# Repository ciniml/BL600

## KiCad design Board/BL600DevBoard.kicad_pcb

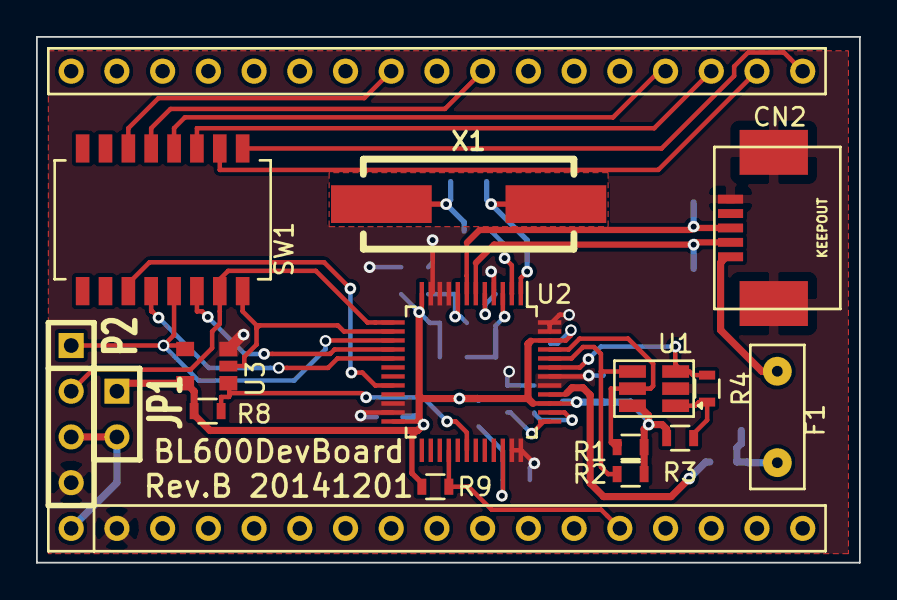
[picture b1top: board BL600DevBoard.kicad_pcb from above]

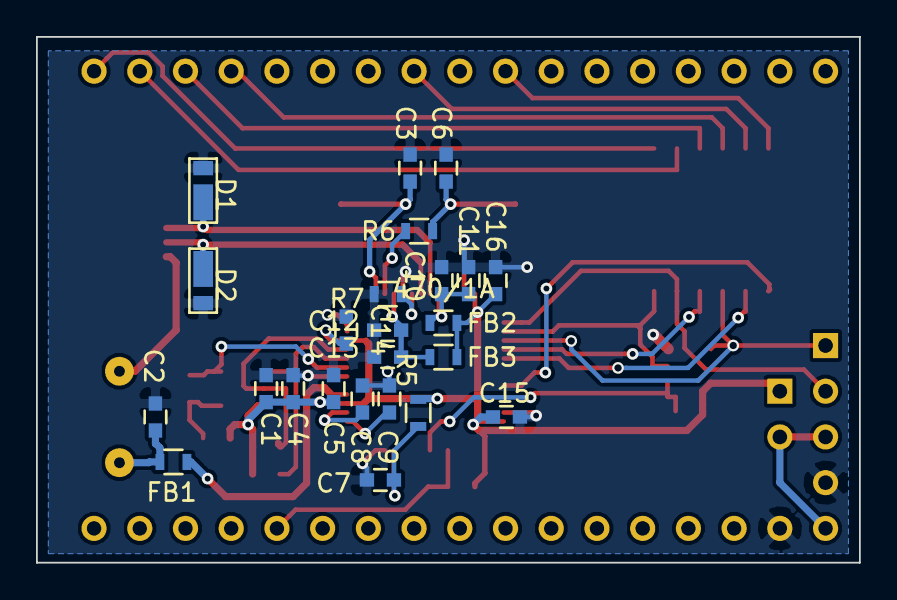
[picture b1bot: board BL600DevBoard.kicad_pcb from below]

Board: 2 copper layers, 45.7 x 29.2 mm, 40 parts (24 on the bottom side), 35 nets.

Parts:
C1, C2, C7, C9: 10n; C_0603
C3, C6: 18p; C_0603
C4, C10, C12: 4.7u; C_0603
C5, C8, C11, C13, C14, C15, C16: 100n; C_0603
CN1: Socket_BL600; SOCKET_BL600
CN2: USB-MINI-B; HIROSE_UX60SC-MB-5ST
D1, D2: UDZV15B; Diode-TUMD2
F1: RXEF050
FB1, FB2, FB3: 470/1A; R_0603
JP1: JUMPER; SIL-2
P2: CONN_BL600_SWDIF; SIL-4
R1, R2, R3, R5, R8, R9: 10k; R_0603
R4: 2k; R_0603
R6: 51; R_0603
R7: 12k; R_0603
SW1: DIPSW_8; 57D-0803
U1: 93C56; SOT-23-6
U2: FT232H; LQFP-48_7x7mm_Pitch0.5mm
U3: TC7SZ125; SC-74A
X1: 12M; Crystal_HC49-SD_SMD

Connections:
/CTS#: SW1.3, U2.16
/DTR#: SW1.5, U2.17
/RI#: SW1.6, U2.20
/SWDCLK_TxD: P2.2, SW1.2, U2.13
/SWDIO_OE: R8.2, U2.30, U3.1
/TDI_RxD: SW1.1, U2.14, U3.2
/TDO_RTS#: P2.1, SW1.4, U2.15, U3.4
/VCC3.3: C1.1, C4.2, C5.2, C14.2, C15.2, C16.2, FB2.1, FB3.1, JP1.1, R1.2, R2.2, R3.2, R5.2, R8.1, R9.1, U1.6, U2.12, U2.24, U2.39, U2.46, U3.5
/VCCA: C9.2, U2.37
/VCORE: C8.2, U2.38
/VPHY: C12.2, C13.2, FB3.2, U2.3
/VPLL: C10.2, C11.2, FB2.2, U2.8
GND: C1.2, C2.1, C3.2, C4.1, C5.1, C6.2, C7.2, C8.1, C9.1, C10.1, C11.1, C12.1, C13.1, C14.1, C15.1, C16.1, CN1.2, CN2.5, CN2.6, CN2.7, D1.1, D2.1, P2.4, R7.2, U1.2, U2.4, U2.9, U2.10, U2.11, U2.22, U2.23, U2.35, U2.36, U2.41, U2.42, U2.47, U2.48, U3.3
unnamed: C2.2, F1.2, FB1.1
unnamed: C3.1, U2.1, X1.1
unnamed: C6.1, R6.2, X1.2
unnamed: C7.1, R5.1, U2.34
unnamed: CN1.1, JP1.2, P2.3
unnamed: CN1.13, R9.2, U2.28
unnamed: CN1.18, SW1.16
unnamed: CN1.19, SW1.15
unnamed: CN1.20, SW1.14
unnamed: CN1.21, SW1.13
unnamed: CN1.25, SW1.12
unnamed: CN1.27, SW1.11
unnamed: CN2.1, F1.1
unnamed: CN2.2, D2.2, U2.6
unnamed: CN2.3, D1.2, U2.7
unnamed: FB1.2, U2.40
unnamed: R1.1, U1.5, U2.45
unnamed: R2.1, U1.4, U2.44
unnamed: R3.1, R4.2, U1.1
unnamed: R4.1, U1.3, U2.43
unnamed: R6.1, U2.2
unnamed: R7.1, U2.5

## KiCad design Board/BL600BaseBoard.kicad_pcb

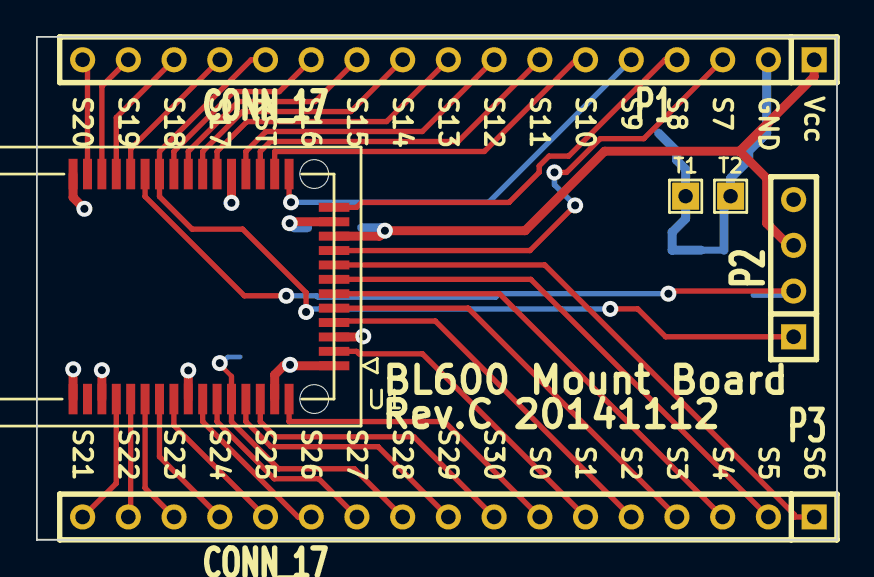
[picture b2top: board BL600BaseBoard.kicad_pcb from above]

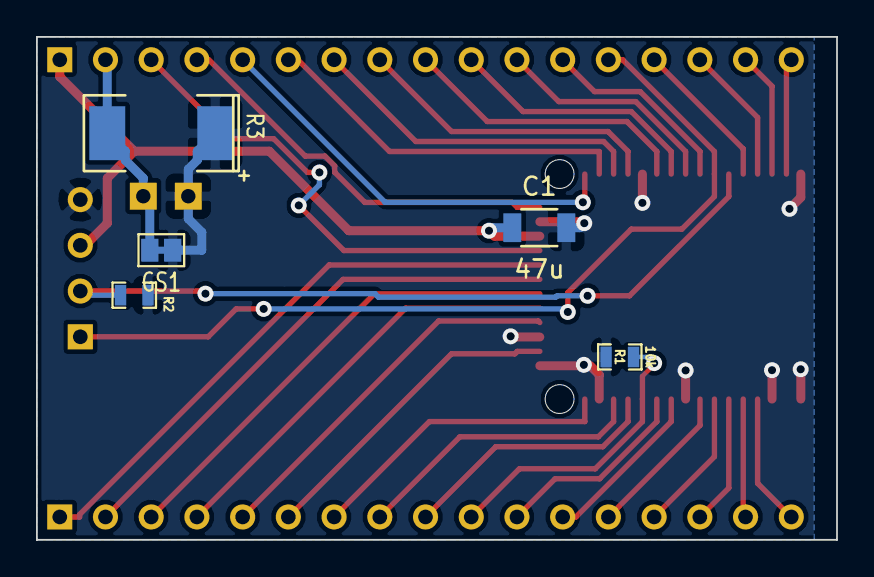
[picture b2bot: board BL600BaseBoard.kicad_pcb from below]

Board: 2 copper layers, 44.5 x 27.9 mm, 11 parts (5 on the bottom side), 36 nets.

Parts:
C1: 47u; C_1206
GS1: GS2; GS2_CLOSED
P1, P3: CONN_17; SIL-17
P2: CONN_4; SIL-4
R1, R2: 10k; SM0603_Resistor
R3: 10m; SM2512
T1, T2: CONN_1; SIL-1
U1: BL600

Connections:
/GND_CN: GS1.2, P1.2, R3.2, T2.1
/SIO_0: P3.7, U1.44
/SIO_1: P3.6, U1.2
/SIO_2: P3.5, U1.4
/SIO_3: P3.4, U1.5
/SIO_4: P3.3, U1.6
/SIO_5: P3.2, U1.7
/SIO_6: P3.1, U1.8
/SIO_7: P1.3, U1.9
/SIO_8: P1.4, U1.12
/SIO_9: P1.5, U1.13
/SIO_10: P1.6, U1.14
/SIO_11: P1.7, U1.15
/SIO_12: P1.8, U1.16
/SIO_13: P1.9, U1.18
/SIO_14: P1.10, U1.19
/SIO_15: P1.11, U1.20
/SIO_16: P1.12, U1.21
/SIO_17: P1.14, U1.24
/SIO_18: P1.15, U1.25
/SIO_19: P1.16, U1.26
/SIO_20: P1.17, U1.27
/SIO_21: P3.17, U1.32
/SIO_22: P3.16, U1.33
/SIO_23: P3.15, U1.34
/SIO_24: P3.14, U1.35
/SIO_25: P3.13, U1.36
/SIO_26: P3.12, U1.38
/SIO_27: P3.11, U1.39
/SIO_28: P3.10, R1.1, U1.40
/SIO_29: P3.9, U1.41
/SIO_30: P3.8, U1.42
/SWDCLK: P2.2, R2.1, U1.23
/VCC: C1.1, P1.1, P2.3, U1.10
/nRESET: P1.13, P2.1, U1.22
GND: C1.2, GS1.1, P2.4, R1.2, R2.2, R3.1, T1.1, U1.1, U1.3, U1.11, U1.17, U1.28, U1.29, U1.31, U1.37, U1.43

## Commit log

2014-04-26 Add a base board schematic, layout, gerber data and solder stencil.
2014-05-17 Add BLE sample codes
2014-07-12 Add swing app
2014-10-24 ベースボードに半田付け時のリファレンスピン用穴を追加
2014-10-24 PWMのサンプルコードを追加
2014-10-24 Smart BasicのSublime Text用構文定義を追加
2014-10-27 Add script to write BL600 firmware
2014-11-10 Add BL600DevBoard and update libraries.
2014-11-10 Add Reflow Oven controller firmware
2014-11-22 Add panelized board cutting path data
2014-11-28 TDI/TDOが入れ替わっている問題を修正
2014-11-28 リフローオーブンの接続パラメータを切断されにくいように変更
2014-12-01 TDI/TDO修正版に基板レイアウトを変更
2014-12-01 U4のリファレンスを欠番になっていたU3に変更。 ACBUS4経由でBL600のリセットを行えるように信号追加。
2014-12-08 不要なバックアップファイルを削除
2014-12-08 openocdのスクリプトにデバッグ用関数を追加。
2014-12-20 ベースボードテスト用スクリプトと電流センサ用スクリプトを追加。
2014-12-26 SublimeTextの構文定義をselect等に対応
